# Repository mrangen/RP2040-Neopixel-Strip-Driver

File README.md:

# RP2040 Neopixel Strip Driver
 A sleek way to control and power common addressible "Neopixel" (WS2812) RGB LED strips using an RP2040 and USB-C.

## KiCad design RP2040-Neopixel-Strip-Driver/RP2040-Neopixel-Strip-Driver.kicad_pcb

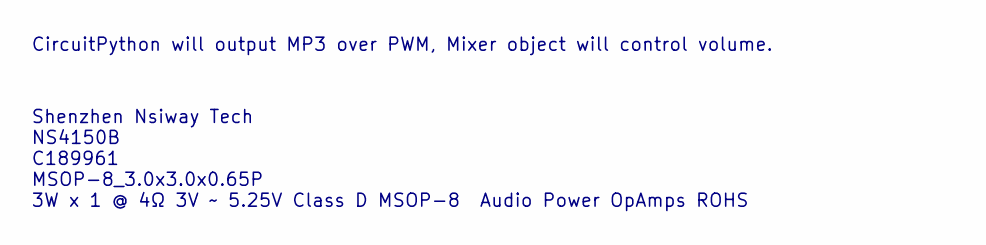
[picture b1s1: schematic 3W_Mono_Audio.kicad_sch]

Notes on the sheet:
Shenzhen Nsiway Tech NS4150B C189961 MSOP-8_3.0x3.0x0.65P 3W x 1 @ 4Ω 3V ~ 5.25V Class D MSOP-8 Audio Power OpAmps ROHS
CircuitPython will output MP3 over PWM, Mixer object will control volume.

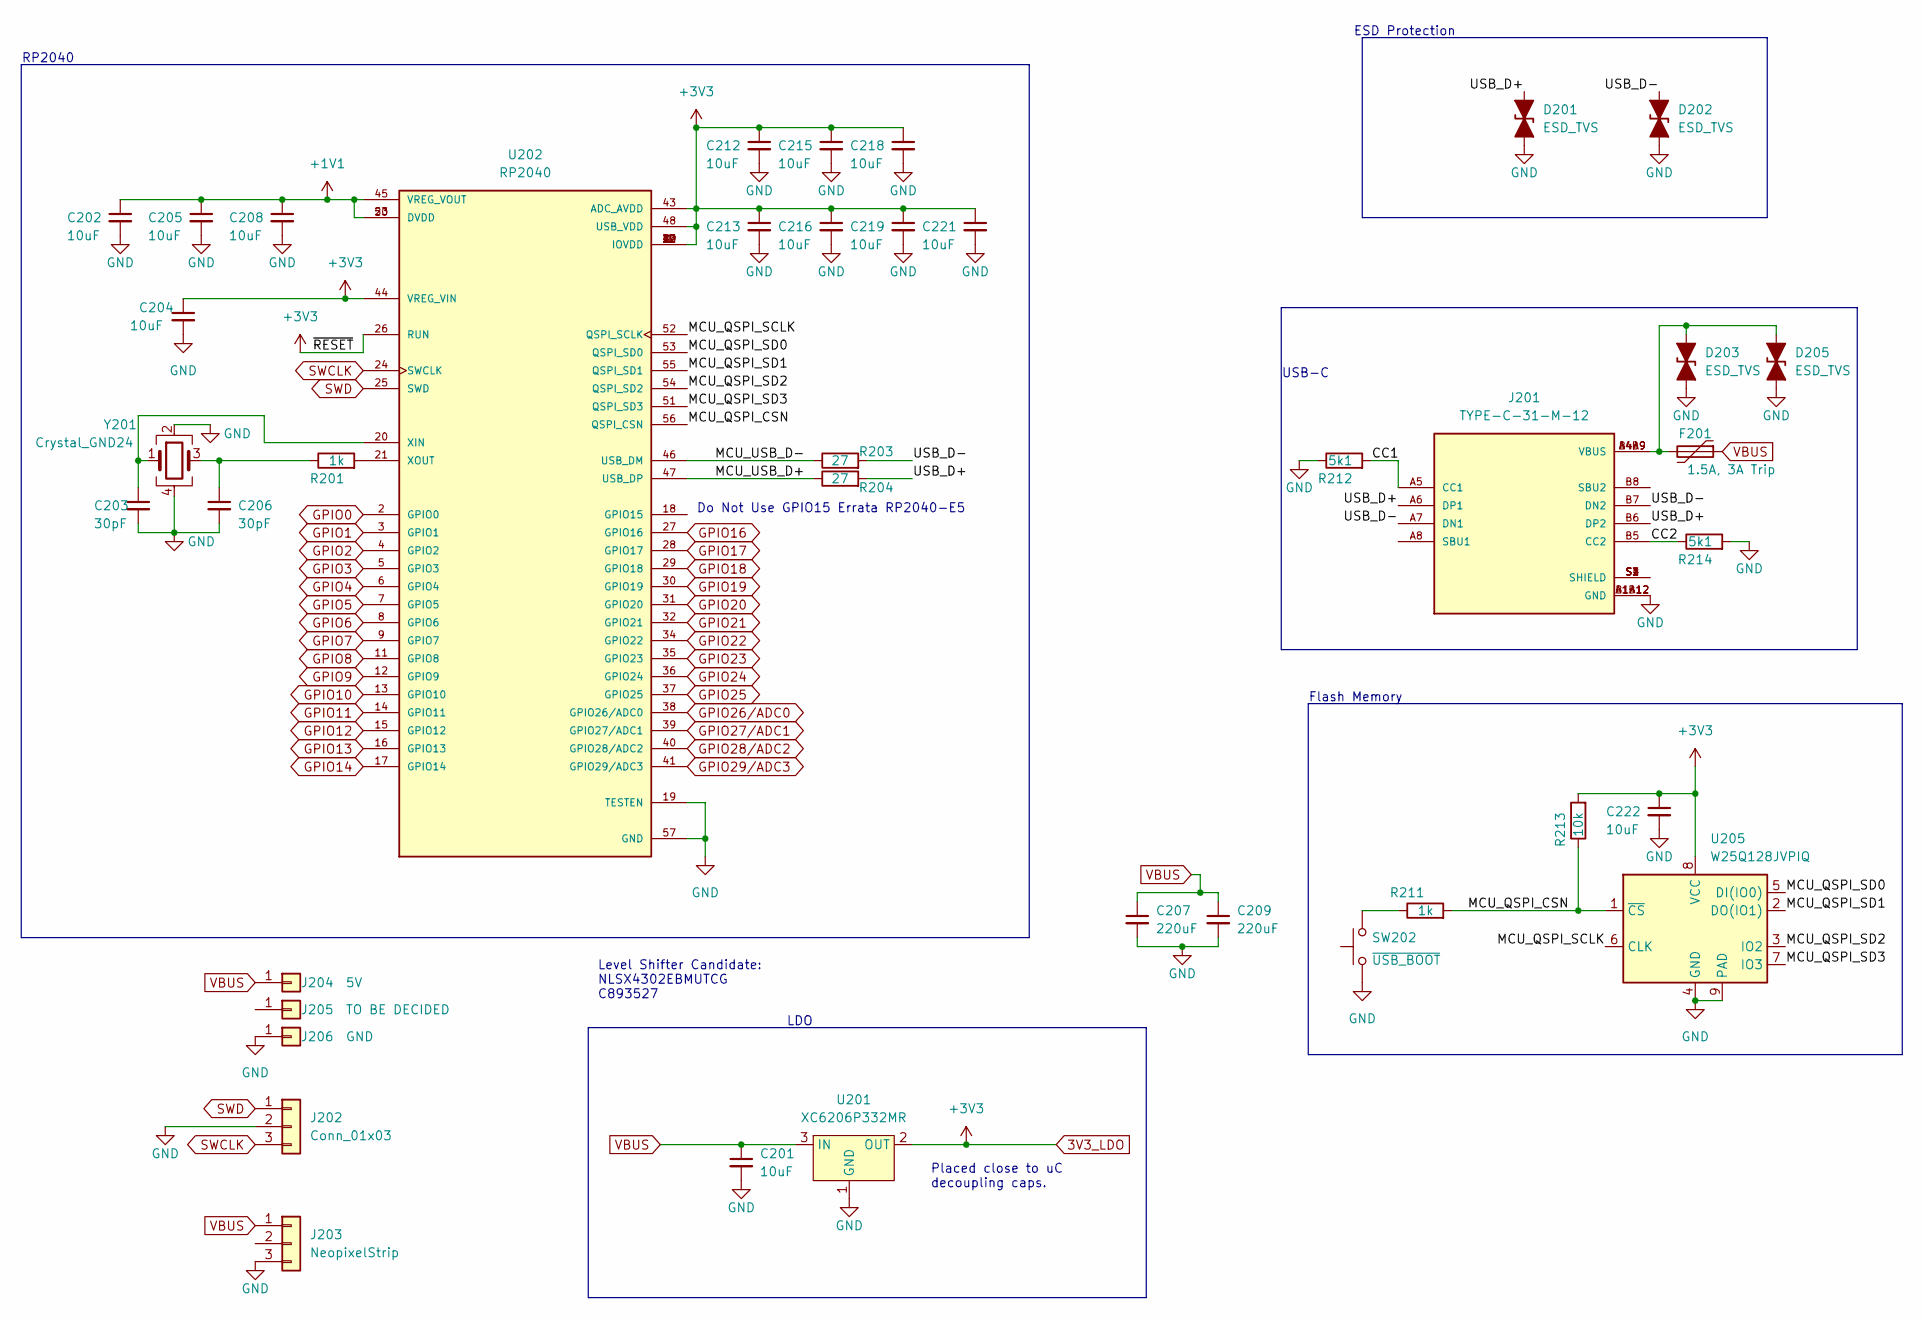
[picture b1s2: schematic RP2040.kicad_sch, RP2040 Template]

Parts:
C201, C202, C204, C205, C208, C212, C213, C215, C216, C218, C219, C221, C222: 10uF; Perfect_0402_Cap; JLCPCB P/N C15525
C203, C206: 30pF; Perfect_0402_Cap; JLCPCB P/N C1570
C207, C209: 220uF; C_1210_3225Metric; JLCPCB P/N C400951
D201, D202, D203, D205: ESD_TVS; Perfect_0402_Resistor; JLCPCB P/N C316049
F201: 1.5A, 3A Trip; R_0805_2012Metric; JLCPCB P/N C70156
J201: TYPE-C-31-M-12; HRO_TYPE-C-31-M-12; PARTREV A; JLCPCB P/N C165948
J202: Conn_01x03; PinHeader_1x03_P2.54mm_Horizontal
J203: NeopixelStrip
J204: 5V; PinSocket_1x01_P2.54mm_Vertical
J205: TO BE DECIDED; PinSocket_1x01_P2.54mm_Vertical
J206: GND; PinSocket_1x01_P2.54mm_Vertical
R201, R211: 1k; Perfect_0402_Resistor; JLCPCB P/N C11702
R203, R204: 27; Perfect_0402_Resistor; JLCPCB P/N C25100
R212, R214: 5k1; Perfect_0402_Resistor; JLCPCB P/N C25905
R213: 10k; Perfect_0402_Resistor; JLCPCB P/N C25744
SW202: ~{USB_BOOT}; GT-TC029B-H025-L1N; JLCPCB P/N C843669
U201: XC6206P332MR; SOT-23; JLCPCB P/N C5446
U202: RP2040; QFN40P700X700X90-57N; PARTREV 1.6.1; JLCPCB P/N C2040
U205: W25Q128JVPIQ; WSON-8-1EP_6x5mm_P1.27mm_EP3.4x4.3mm; JLCPCB P/N C190862
Y201: Crystal_GND24; OSC_X322516MLB4SI; JLCPCB P/N C9002

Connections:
3V3_LDO: C204.1, C212.1, C213.1, C215.1, C216.1, C218.1, C219.1, C221.1, C222.1, R213.2, U201.2 (OUT), U202.1 (IOVDD), U202.10 (IOVDD), U202.22 (IOVDD), U202.26 (RUN), U202.33 (IOVDD), U202.42 (IOVDD), U202.43 (ADC_AVDD), U202.44 (VREG_VIN), U202.48 (USB_VDD), U202.49 (IOVDD), U205.8 (VCC)
+1V1: C202.1, C205.1, C208.1, U202.23 (DVDD), U202.45 (VREG_VOUT), U202.50 (DVDD)
/RP2040/CC1: J201.A5 (CC1), R212.2
/RP2040/CC2: J201.B5 (CC2), R214.1
/RP2040/MCU_QSPI_CSN: R211.2, R213.1, U202.56 (QSPI_CSN), U205.1 (~CS)
/RP2040/MCU_QSPI_SCLK: U202.52 (QSPI_SCLK), U205.6 (CLK)
/RP2040/MCU_QSPI_SD0: U202.53 (QSPI_SD0), U205.5 (DI(IO0))
/RP2040/MCU_QSPI_SD1: U202.55 (QSPI_SD1), U205.2 (DO(IO1))
/RP2040/MCU_QSPI_SD2: U202.54 (QSPI_SD2), U205.3 (IO2)
/RP2040/MCU_QSPI_SD3: U202.51 (QSPI_SD3), U205.7 (IO3)
/RP2040/MCU_USB_D+: R204.1, U202.47 (USB_DP)
/RP2040/MCU_USB_D-: R203.1, U202.46 (USB_DM)
/RP2040/USB_D+: D201.2 (A2), J201.A6 (DP1), J201.B6 (DP2), R204.2
/RP2040/USB_D-: D202.2 (A2), J201.A7 (DN1), J201.B7 (DN2), R203.2
GND: C201.2, C202.2, C203.2, C204.2, C205.2, C206.2, C207.2, C208.2, C209.2, C212.2, C213.2, C215.2, C216.2, C218.2, C219.2, C221.2, C222.2, D201.1 (A1), D202.1 (A1), D203.1 (A1), D205.1 (A1), J201.A1B12 (GND), J201.B1A12 (GND), J202.2, J203.3, J206.1, R212.1, R214.2, SW202.1, U201.1 (GND), U202.19 (TESTEN), U202.57 (GND), U205.4 (GND), U205.9 (PAD), Y201.2, Y201.4
GPIO0: U202.2 (GPIO0)
GPIO1: U202.3 (GPIO1)
GPIO2: U202.4 (GPIO2)
GPIO3: U202.5 (GPIO3)
GPIO4: U202.6 (GPIO4)
GPIO5: U202.7 (GPIO5)
GPIO6: U202.8 (GPIO6)
GPIO7: U202.9 (GPIO7)
GPIO8: U202.11 (GPIO8)
GPIO9: U202.12 (GPIO9)
GPIO10: U202.13 (GPIO10)
GPIO11: U202.14 (GPIO11)
GPIO12: U202.15 (GPIO12)
GPIO13: U202.16 (GPIO13)
GPIO14: U202.17 (GPIO14)
GPIO16: U202.27 (GPIO16)
GPIO17: U202.28 (GPIO17)
GPIO18: U202.29 (GPIO18)
GPIO19: U202.30 (GPIO19)
GPIO20: U202.31 (GPIO20)
GPIO21: U202.32 (GPIO21)
GPIO22: U202.34 (GPIO22)
GPIO23: U202.35 (GPIO23)
GPIO24: U202.36 (GPIO24)
GPIO25: U202.37 (GPIO25)
GPIO26/ADC0: U202.38 (GPIO26/ADC0)
GPIO27/ADC1: U202.39 (GPIO27/ADC1)
GPIO28/ADC2: U202.40 (GPIO28/ADC2)
GPIO29/ADC3: U202.41 (GPIO29/ADC3)
unnamed: C203.1, U202.20 (XIN), Y201.1
unnamed: C206.1, R201.1, Y201.3
unnamed: D203.2 (A2), D205.2 (A2), F201.2, J201.A4B9 (VBUS), J201.B4A9 (VBUS)
unnamed: J201.S1 (SHIELD), J201.S2 (SHIELD), J201.S3 (SHIELD), J201.S4 (SHIELD)
unnamed: R201.2, U202.21 (XOUT)
unnamed: R211.1, SW202.2
SWCLK: J202.3, U202.24 (SWCLK)
SWD: J202.1, U202.25 (SWD)
VBUS: C201.1, C207.1, C209.1, F201.1, J203.1, J204.1, U201.3 (IN)

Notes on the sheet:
RP2040
Flash Memory
LDO
ESD Protection
Level Shifter Candidate: NLSX4302EBMUTCG C893527
Placed close to uC decoupling caps.
USB-C
Do Not Use GPIO15 Errata RP2040-E5

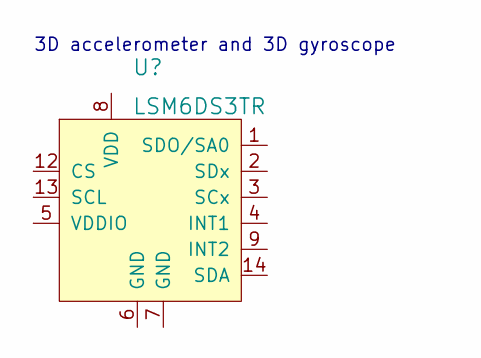
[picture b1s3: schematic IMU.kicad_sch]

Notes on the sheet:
3D accelerometer and 3D gyroscope

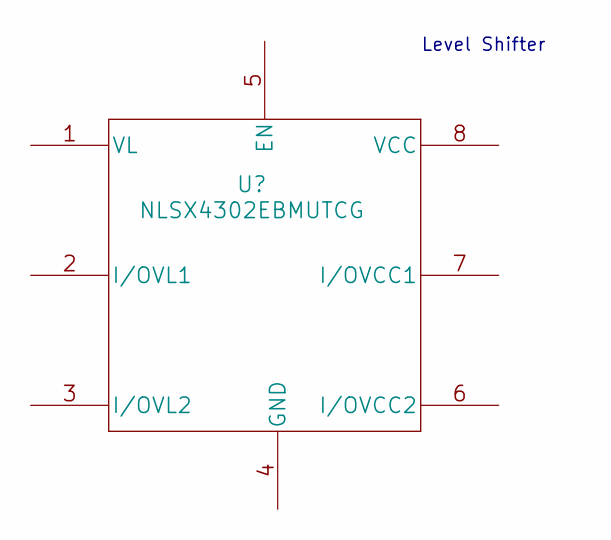
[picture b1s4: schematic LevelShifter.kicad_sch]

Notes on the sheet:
Level Shifter

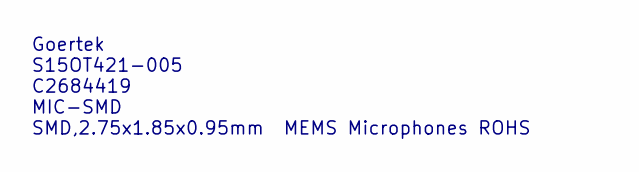
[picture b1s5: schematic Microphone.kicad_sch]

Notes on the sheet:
Goertek S15OT421-005 C2684419 MIC-SMD SMD,2.75x1.85x0.95mm MEMS Microphones ROHS

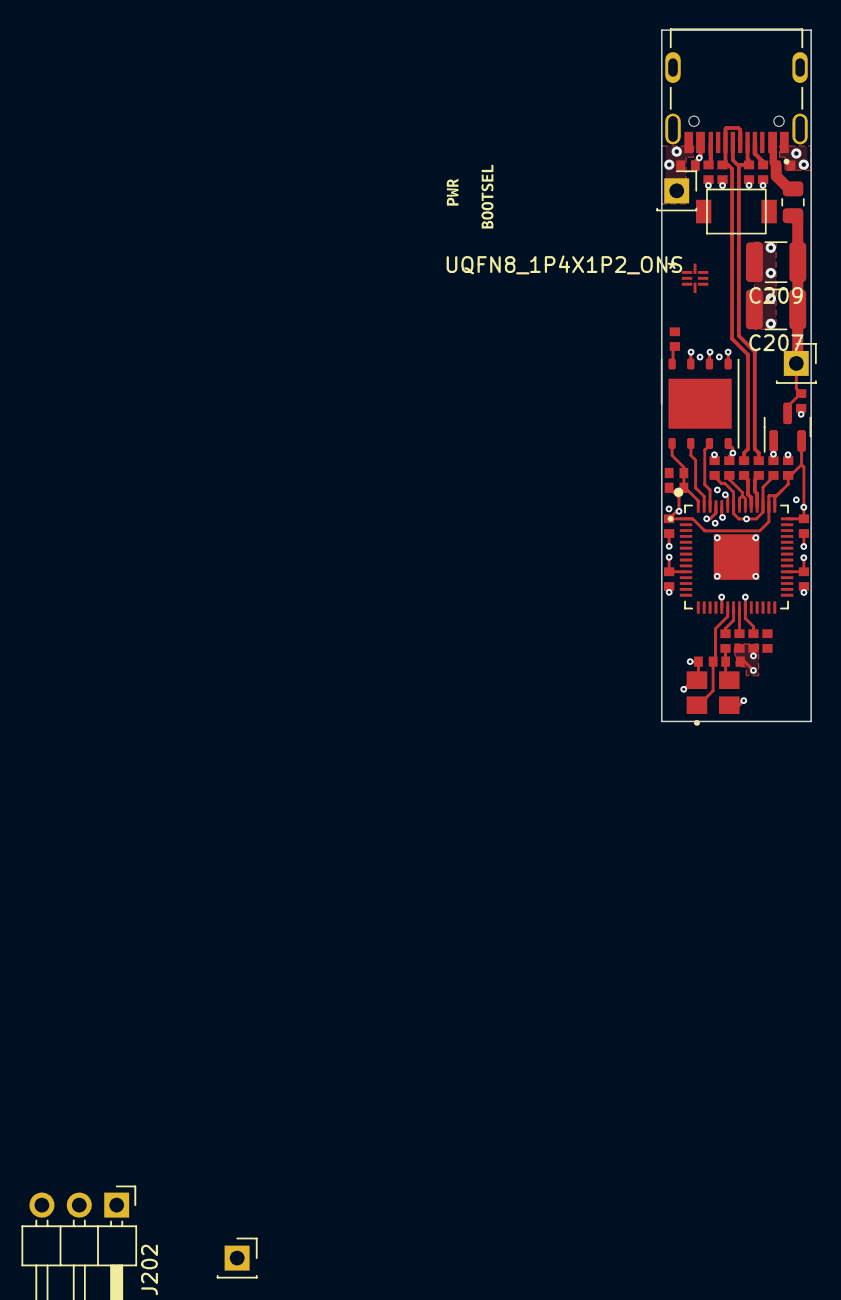
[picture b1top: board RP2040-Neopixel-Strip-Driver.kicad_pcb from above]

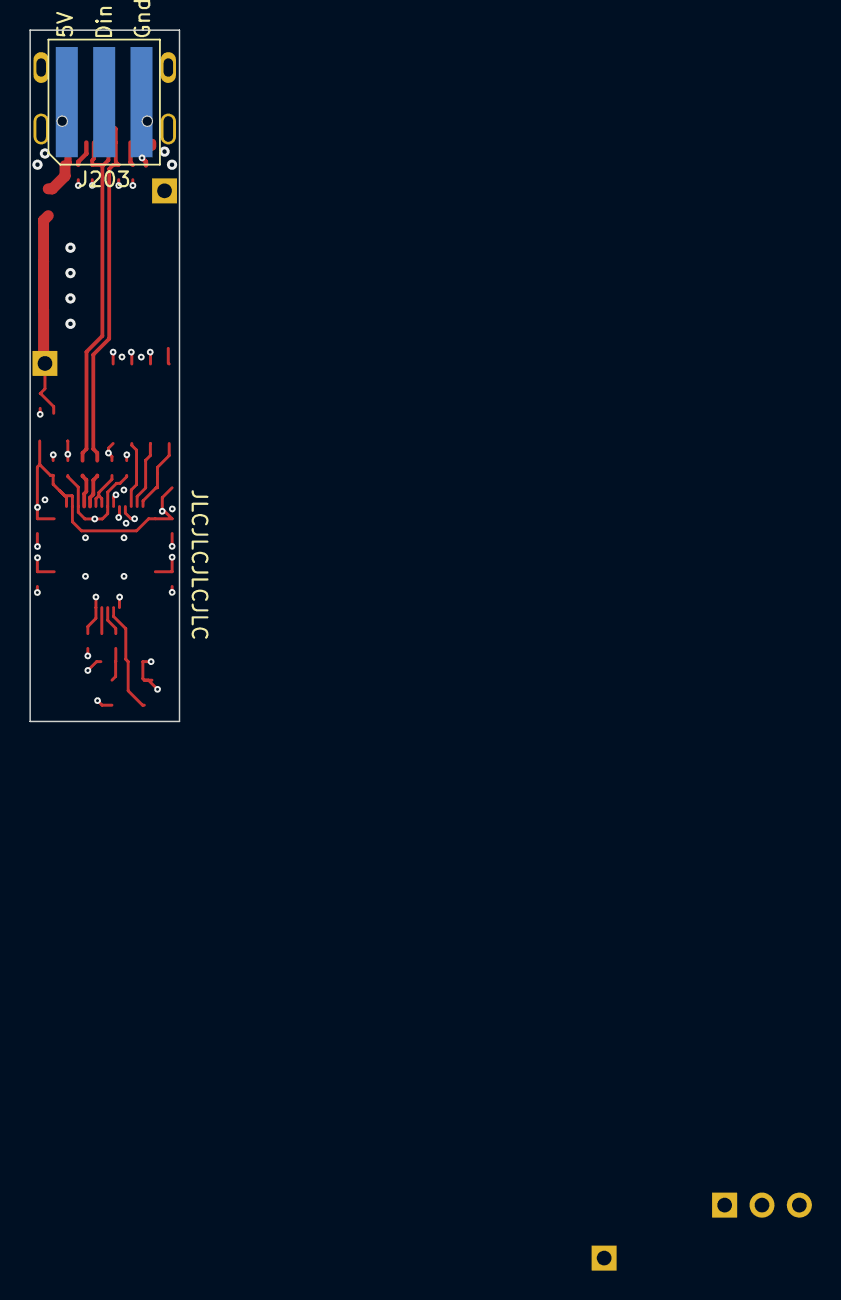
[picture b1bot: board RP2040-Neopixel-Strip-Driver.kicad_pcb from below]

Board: 4 copper layers, 10.2 x 47.0 mm, 49 parts (4 on the bottom side), 24 nets.

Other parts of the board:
U101: UQFN8_1P4X1P2_ONS; NLSX4302EBMUTCG
kibuzzard-6265A538: G***; kibuzzard-6265A538
kibuzzard-62659E4E: G***; kibuzzard-62659E4E
kibuzzard-62659F2B: G***; kibuzzard-62659F2B
kibuzzard-628425F6: G***; kibuzzard-628425F6
kibuzzard-6284261D: G***; kibuzzard-6284261D
kibuzzard-62842605: G***; kibuzzard-62842605
kibuzzard-62842613: G***; kibuzzard-62842613
kibuzzard-62842635: G***; kibuzzard-62842635

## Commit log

2022-07-01 Stripped down RP2040 Template, added Neopixel Strip
2022-07-02 Made new LED strip model and narrowed board.
2022-07-04 Continued to shrink PCB, replaced regulator and mem with smaller ICs, removed 1206 caps
2022-07-04 Continued to shrink board.
2022-07-04 Added bulk decoupling capacitors and PTC resetable fuse, planning level shifter.
2022-07-04 Worked on layout, still selecting a level shifter.
2022-07-05 Added level shifter
2022-07-05 Added model for level shifter and added 3Daccelerometer+3Dgyroscope
2022-07-08 Project Expansion/Pivot - This is now a very involved cosplay prop tool.
    Looking to incorporate a lot:
    3D Gyro + 3D Accelerometer
    Neopixel Driver
    Speaker Driver
    Microphone
    SD Card Connector
2022-07-09 Made microphone symbol, footprint, and 3D model.
2022-07-10 Added Motor Driver
2022-07-10 Moved USB and 3.3V Regulator from RP2040 to Power Sheet
2022-07-10 Reworked the USB-C Connector Symbol to clean up schematic
2022-07-10 Removed unnecessary pwr and gnd pins, moved decoupling caps to power sheet
2022-07-10 Created symbol for Audio Amp, associated footprint and model from KiCad library
2022-07-10 Updated all IC symbols to have filled background, personal preference.
2022-07-10 Changed name of sheet.
2022-07-10 Found diode for power supply ORing
2022-07-12 Added Pico W
2022-07-13 Removed RP2040 Schematic, Going with Pico W Module
2022-07-13 Added buck converter IC

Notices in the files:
RP2040-Neopixel-Strip-Driver/RP2040-Neopixel-Strip-Driver.kicad_pcb:
MIT License
parts and their libraries:
Copyright 2021 Accelerated Designs. All rights reserved.
